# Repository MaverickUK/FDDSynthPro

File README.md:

# FDD Synth Duo

An RP2350 that pretends to be a 3.5-inch floppy drive, GoTek style, as the base for a future FDD Synth that *is* the drive rather than one that listens to it. Being the drive, it knows exactly when the motor spins and how the head moves, so the sounds can follow every step.

At this stage it is a proof of concept on an Olimex RP2350-PICO2-BB48, tested from the same Mac that builds it. The host is a Feather RP2040 with an Adafruit Floppy FeatherWing, running Adafruit's Greaseweazle-compatible firmware, so the Greaseweazle tools (`gw`) drive it. See [docs/plan.md](docs/plan.md) for the slices and [docs/wiring.md](docs/wiring.md) for the connections. [docs/bringup.md](docs/bringup.md) is the checklist for hardware day, [docs/parts.md](docs/parts.md) the parts list, and [docs/wiring.html](docs/wiring.html) an interactive wiring diagram with a soldering checklist (open it in a browser).

It follows the approach of [HDDSynthPro](https://github.com/MaverickUK/HDDSynthPro), which does the same for IDE hard disks.

## See and hear it

A 36-second showreel, with sound (click to play). A virtual PC uses a FAT12 disk while the front panel is worked: a disk chosen and swapped in, boot and `DIR`, reads with the volume turned down, the head trace following a long seek, a save, motor off and an eject. The screens, the drive and the sound are all the firmware's own code, run on the Mac in simulated real time, with the sample pack cut from a recording of a real drive (`samples/Recorded`). `scripts/make_showreel.py` makes it. (The link plays it through jsDelivr, which serves the repo's copy as a video; GitHub's own link would download it.)

## Status

Slice 0 (listen only): the firmware records every drive select, motor, side, density and write-gate change and every head step it sees, without driving any pin, and streams the trace over USB serial.

The drive build (`pio run -e bb48_drive`, slices 1-3) is ready for when the hardware arrives:
- it tracks the head, and drives TRK00, a 300 or 360 RPM index, write protect and disk change (or READY, for Shugart hosts);
- it streams an image from the SD card on RDATA, or, without one, a welcome disk whose `README.TXT` (from [welcome/README.TXT](welcome/README.TXT)) explains how to set the drive up: PC disks from 160 KB to 1.68 MB (5.25- and 3.5-inch) by their size, and other machines' disks, MFM or FM (Roland, Ensoniq, Kaypro, the Osborne 1, 8-inch CP/M and the like), from GoTek's `IMG.CFG`;
- it serves HFE flux images too: tracks as recorded, so copy-protected disks keep their bad CRCs, long tracks and weak bits;
- it takes writes back into the image, from single sectors to whole tracks;
- it swaps between the images on the card, GoTek style, whatever their formats;
- it answers as drive A or B, past a twist or on a straight cable, or as Shugart DS0–DS2; or as two drives at once, each with its own disk ([docs/config.md](docs/config.md));
- it reports what it does as sound events (motor, clicks, seeks, bumps against the end stops, disk changes), and plays them with a sample pack through an I2S amp: the FDD Synth. See [docs/activity.md](docs/activity.md), `samples/Recorded/` for a sample pack cut from a recording of a real drive, and `samples/Placeholder/` for a synthesised stand-in.

Its logic is tested on the Mac against virtual hosts (the Feather's firmware and a Greaseweazle's), and its PIO program in a simulator whose output Greaseweazle's own decoder reads back. It has not run on hardware yet.

## Front panel

An SSD1306 OLED on the BB48's Qwiic socket, a rotary encoder and an action button, as on the HDD Synth. Turn for the volume; press to pick a disk from the card and insert it; the action button steps through the screens, and holding it ejects the disk. On the Sounds screen, press to choose the sample pack. Like a GoTek, it remembers the disk, the pack and the volume across power-off. [docs/oled](docs/oled) has every screen, drawn by the firmware's own code.

## Quick start

```sh
test/run_native_tests.sh                 # C++ unit tests (no hardware)
brew install mtools dosfstools           # for the DOS disk tests
cd host && python3 -m venv .venv && .venv/bin/pip install -r requirements.txt
.venv/bin/pytest                         # simulator and parser tests (no hardware)

pio run -t upload                        # build and flash the BB48
pio device monitor                       # h help, p pin levels, s stats

scripts/rig.sh -m slice0                 # everything, against the real host
```

Read the power-order rule in [docs/wiring.md](docs/wiring.md) before connecting the host.

## Licence

To be decided (HDDSynth_Native is GPL-3.0).

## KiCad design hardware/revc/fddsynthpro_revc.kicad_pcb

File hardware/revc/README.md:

# FDD Synth Duo rev C board

The integrated board: the RP2350B with its flash and PSRAM, the microSD socket, the floppy interface, the MAX98357A amp, and power from the floppy power connector or USB-C, on rev B's outline (the HDD Synth MK5's). The design and the reasons for it are in [docs/pcb-revc.md](../../docs/pcb-revc.md); the sled that fits it in a 3.5-inch bay is [hardware/mount/fddsynthpro_bay.scad](../mount/fddsynthpro_bay.scad).

Status: **not reviewed, not ordered.** The schematic passes ERC with 0 violations, and its netlist test passes. The board is placed and autorouted: DRC with schematic parity finds 0 unconnected items and 0 parity issues; its 7 warnings are connector outlines overhanging the edge, as meant. `build.sh` rebuilds and checks it all.

## Files

| File | What |
|---|---|
| `fddsynthpro_revc.kicad_pro` | The project: open this in KiCad 10 |
| `fddsynthpro_revc.kicad_sch` | Root sheet, with one sheet per block: `power`, `mcu` (RP2350B, flash, PSRAM), `floppy`, `audio` (the amp and the panel headers), `sd` |
| `fddsynthpro_revc.kicad_pcb` | The board: 4 layers (signals, GND plane, 3V3 plane, signals) |
| `fddsynthpro_revc.kicad_dru` | One rule: 0.125 mm spacing inside Raspberry Pi's regulator layout only (HDDSynthPro's) |
| `FDDSynthProRevC.kicad_sym`, `FDDSynthProRevC.pretty/` | The SN7407 and LM66200 symbols; the floppy power header's footprint; the logo; Raspberry Pi's inductor and wide-0402 footprints and the TF PUSH microSD socket (HDDSynthPro's) |
| `tools/gen_schematic.py` | Generates the schematic, with each part's LCSC number |
| `tools/layout_pcb.py` | Places the parts, Raspberry Pi's regulator copper and the planes |
| `tools/autoroute.py` | Routes with Freerouting, then pours ground on the outer layers |
| `tools/make_logo.py` | Makes the silkscreen logo and the easter egg on the back (board-only footprints) from `media/FDDSynthDuo.png` and `media/dont-copy-that-floppy.png` |
| `tools/add_parts.py` | Adds parts the schematic has gained to the routed board, or moves parts on it (`--move`), so only their nets get routed |

The generators follow HDDSynthPro's (`../../HDDSynthPro/hardware/tools`). They bootstrap the design: once the files are edited in KiCad, those edits are the source, and rerunning a generator overwrites them.

To add a small part to the routed board without routing it all again (where there's room: the series resistors on the floppy inputs needed a full reroute, `build.sh`): add it to `gen_schematic.py` and to `PLACE` in `layout_pcb.py`, then

```sh
python tools/gen_schematic.py
"$KICAD_PYTHON" tools/add_parts.py prepare      # places it, locks the routing that's there
                                               # (or: prepare --move J5, to move a part and reroute its nets;
                                               #  prepare --rip NET, to route one net again)
FREEROUTING=... JAVA=... "$KICAD_PYTHON" tools/autoroute.py
"$KICAD_PYTHON" tools/add_parts.py finish       # unlocks it again
./build.sh --silkscreen
```

## Building and checking it

KiCad 10 is needed (the files are KiCad 10's format). On the Windows machine, a portable KiCad 10 lives in `%LOCALAPPDATA%\Programs\kicad10-portable`. It was unpacked from the installer, so it needs no admin rights, and its `env.sh` sets `KICAD_CLI`, `KICAD_PYTHON` and the library paths. Freerouting 2.5.0 and a Java 25 runtime are in `%LOCALAPPDATA%\Programs\freerouting`.

```sh
. "$LOCALAPPDATA/Programs/kicad10-portable/env.sh"
cd hardware/revc
python tools/gen_schematic.py                                   # the schematic
"$KICAD_CLI" sch erc fddsynthpro_revc.kicad_sch                 # expect 0 violations
"$KICAD_PYTHON" tools/layout_pcb.py                             # placement (overwrites the board)
FREEROUTING=<freerouting-2.5.0.jar> JAVA=<java.exe> "$KICAD_PYTHON" tools/autoroute.py
"$KICAD_CLI" pcb drc --refill-zones --save-board --schematic-parity fddsynthpro_revc.kicad_pcb
cd ../../host && KICAD_CLI="$KICAD_CLI" pytest tests/test_revc_schematic.py   # the netlist against src/config.h
```

On the Mac, KiCad's own paths work as for rev B: `KICAD_SHARE=/Applications/KiCad/KiCad.app/Contents/SharedSupport`, and KiCad's bundled Python for the layout and routing scripts.

## Ordering

Every part carries its LCSC number in a `LCSC Part Number` field (the Fabrication Toolkit plugin reads it). [docs/pcb-revc.md](../../docs/pcb-revc.md) lists the parts and their stock on 8 Nov 2026. Check these before ordering:
- **L1** (Raspberry Pi's 3.3 µH inductor) was out of stock.
- **The 16 MB flash** was down to 20.
- **J12,** the HDD Synth-style speaker terminal, is marked DNP (not fitted).
- **Solder mask:** the RP2350B (U1), USB-C (J9) and LM66200 (U6) footprints are copies of KiCad's (`gen_schematic.py`'s `one_mask_opening()`) with one mask opening per row of fine-pitch pads. Their pads are 0.2 mm apart, and PCBWay can't make a strip of black mask under 0.22 mm (it asked about the IDE Synth Bay's QFN-80, 11 Nov 2026). The narrowest strip left is 0.25 mm, so black mask needs no special request.
- **JLCPCB's placement preview:** check the rotations, above all the QFN-80, the inductor's polarity dot, the SOT-583, the TQFN-16 and the right-angle J1.

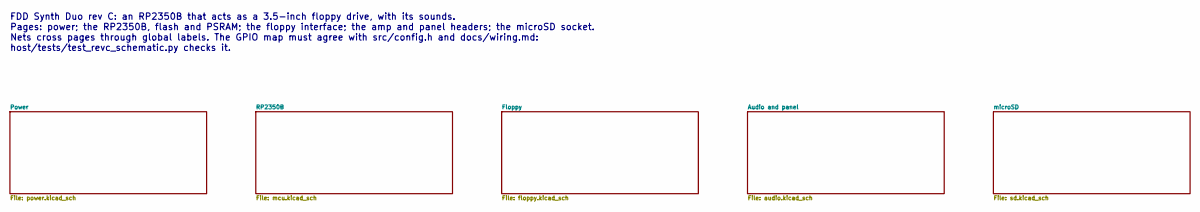
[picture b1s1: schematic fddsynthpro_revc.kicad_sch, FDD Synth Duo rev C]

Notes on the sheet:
FDD Synth Duo rev C: an RP2350B that acts as a 3.5-inch floppy drive, with its sounds. Pages: power; the RP2350B, flash and PSRAM; the floppy interface; the amp and panel headers; the microSD socket. Nets cross pages through global labels. The GPIO map must agree with src/config.h and docs/wiring.m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

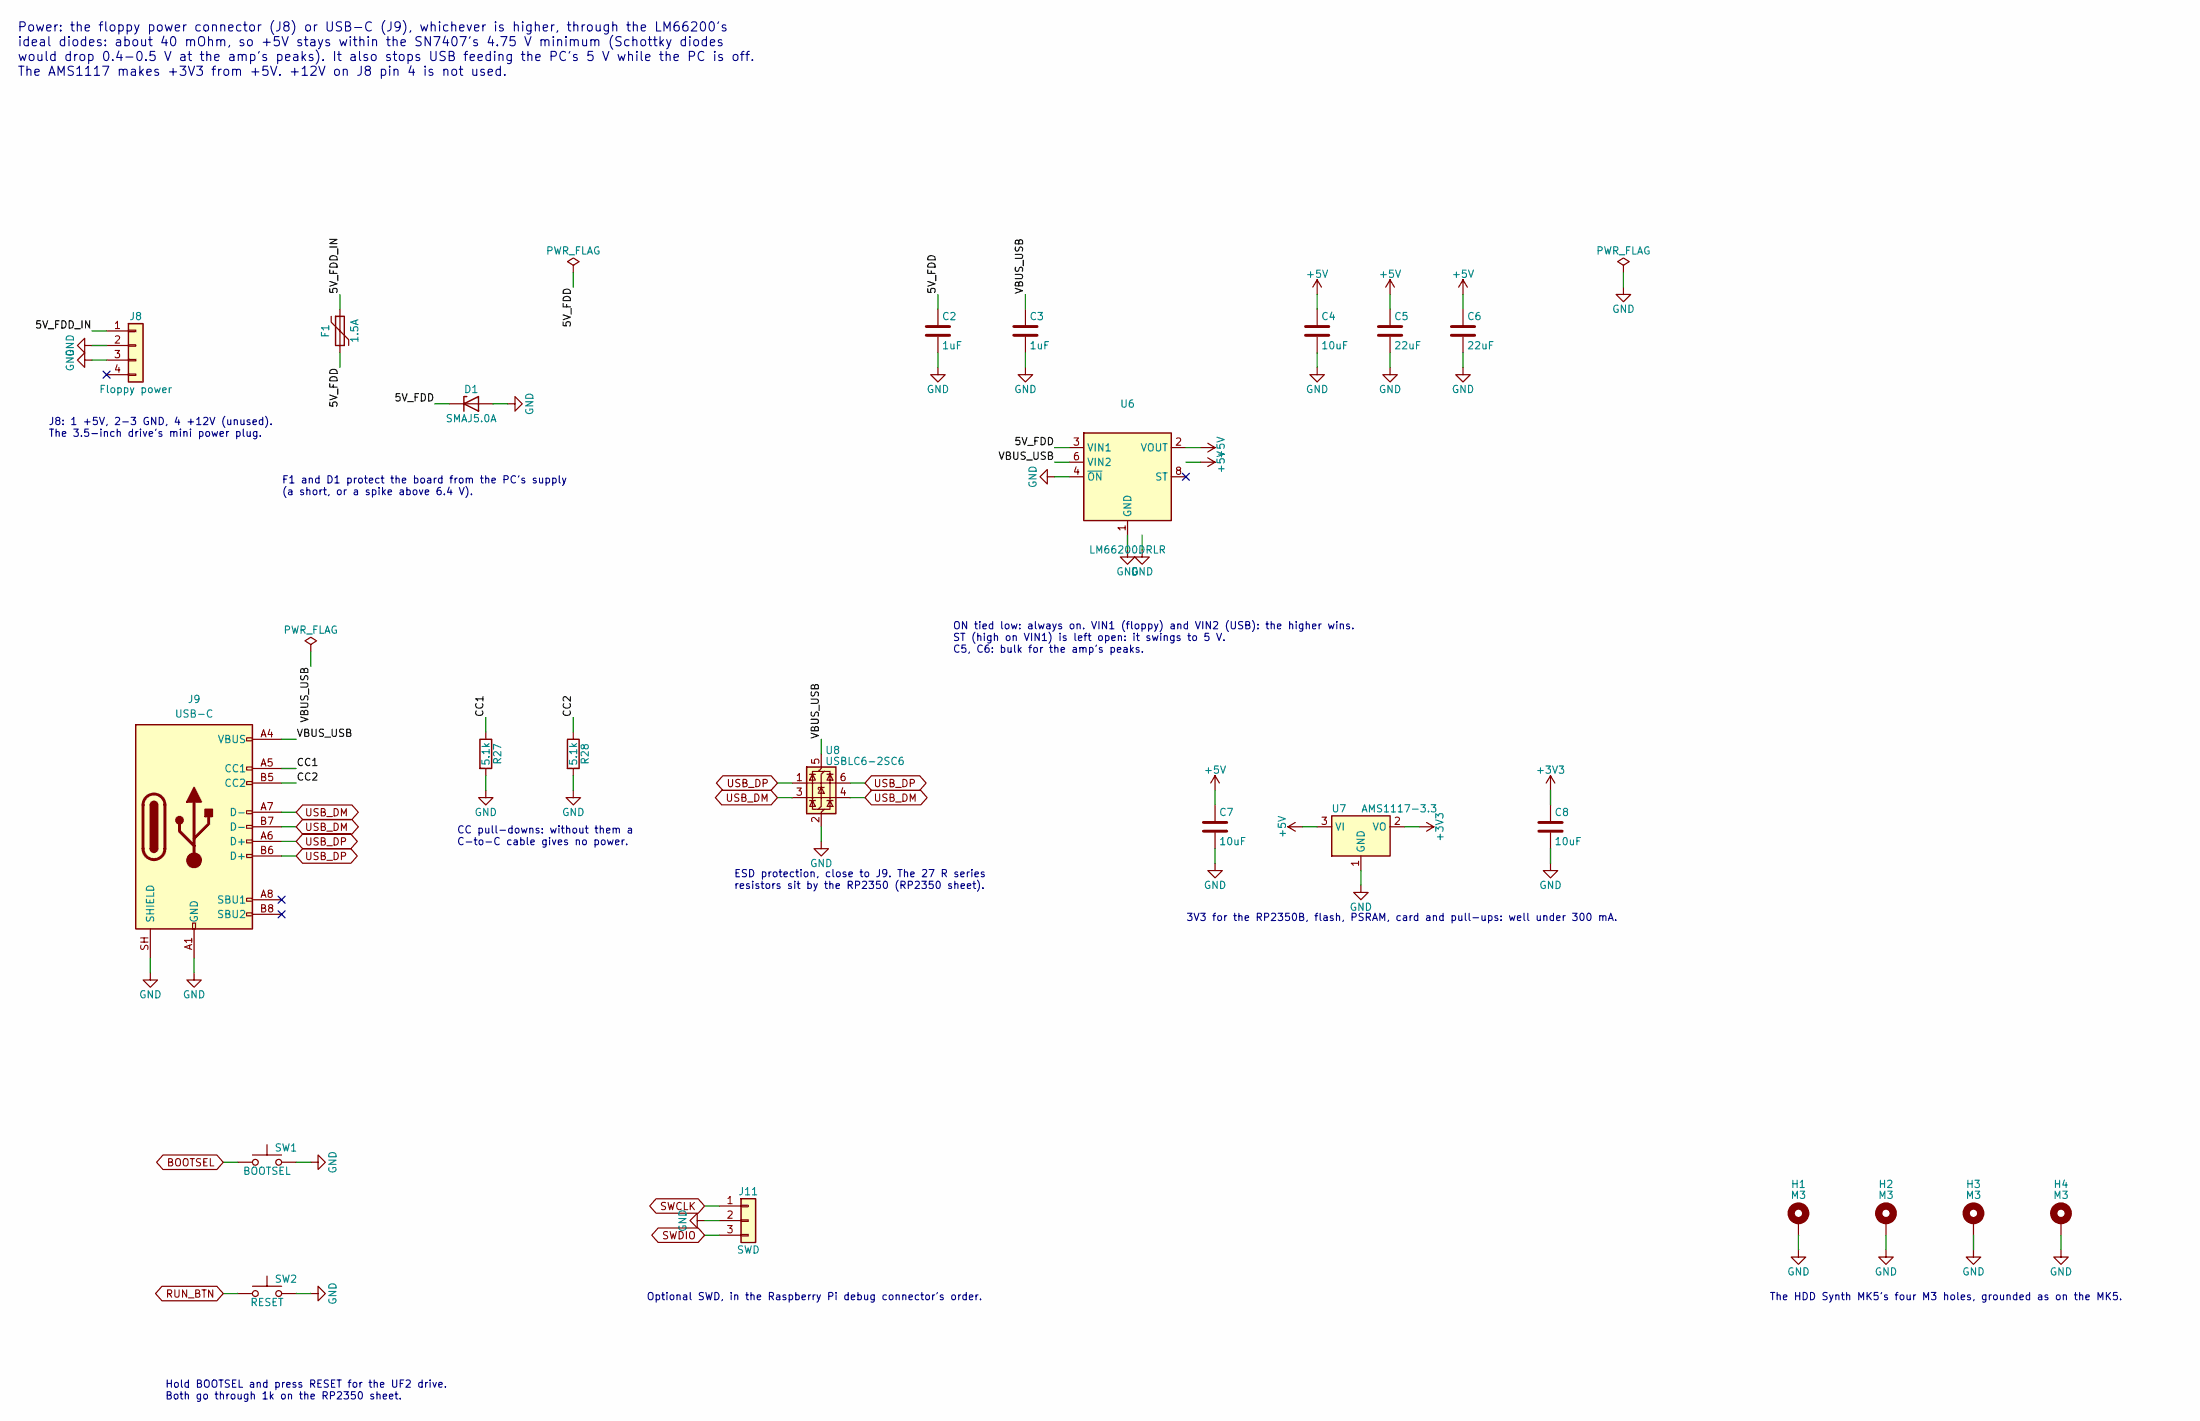
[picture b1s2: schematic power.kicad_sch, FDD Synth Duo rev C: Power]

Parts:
C2, C3: 1uF; C_0402_1005Metric; LCSC Part Number C52923
C4, C7, C8: 10uF; C_0805_2012Metric; LCSC Part Number C15850
C5, C6: 22uF; C_0603_1608Metric; LCSC Part Number C59461
D1: SMAJ5.0A; D_SMA; LCSC Part Number C113952
F1: 1.5A; Fuse_1206_3216Metric; LCSC Part Number C2830250
H1, H2, H3, H4: M3; MountingHole_3.2mm_M3_Pad
J8: Floppy power; TE_171825-4_1x04_P2.50mm_Vertical; MPN TE 171825-4; LCSC Part Number C210162
J9: USB-C; USB_C_Receptacle_HRO_TYPE-C-31-M-12_OneMaskOpening; MPN HRO TYPE-C-31-M-12; LCSC Part Number C165948
J11: SWD; PinHeader_1x03_P2.54mm_Vertical; LCSC Part Number C124376
R27, R28: 5.1k; R_0603_1608Metric; LCSC Part Number C23186
SW1: BOOTSEL; SW_Push_1P1T_XKB_TS-1187A; LCSC Part Number C318884
SW2: RESET; SW_Push_1P1T_XKB_TS-1187A; LCSC Part Number C318884
U6: LM66200DRLR; SOT-583-8_OneMaskOpening; LCSC Part Number C3235556
U7: AMS1117-3.3; SOT-223-3_TabPin2; LCSC Part Number C6186
U8: USBLC6-2SC6; SOT-23-6; LCSC Part Number C2687116

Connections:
+3V3: C8.1, U7.2 (VO); also elsewhere on the board
+5V: C4.1, C5.1, C6.1, C7.1, U6.2 (VOUT), U6.7 (VOUT), U7.3 (VI); also elsewhere on the board
/Power/5V_FDD: C2.1, D1.1 (K), F1.2, U6.3 (VIN1)
/Power/5V_FDD_IN: F1.1, J8.1
/Power/CC1: J9.A5 (CC1), R27.1
/Power/CC2: J9.B5 (CC2), R28.1
/Power/VBUS_USB: C3.1, J9.A4 (VBUS), J9.A9 (VBUS), J9.B4 (VBUS), J9.B9 (VBUS), U6.6 (VIN2), U8.5 (VBUS)
BOOTSEL: SW1.1; also elsewhere on the board
GND: C2.2, C3.2, C4.2, C5.2, C6.2, C7.2, C8.2, D1.2 (A), H1.1, H2.1, H3.1, H4.1, J8.2, J8.3, J9.A1 (GND), J9.A12 (GND), J9.B1 (GND), J9.B12 (GND), J9.SH (SHIELD), J11.2, R27.2, R28.2, SW1.2, SW2.2, U6.1 (GND), U6.4 (~ON), U6.5 (GND), U7.1 (GND), U8.2 (GND); also elsewhere on the board
RUN_BTN: SW2.1; also elsewhere on the board
SWCLK: J11.1; also elsewhere on the board
SWDIO: J11.3; also elsewhere on the board
USB_DM: J9.A7 (D-), J9.B7 (D-), U8.3 (I/O2), U8.4 (I/O2); also elsewhere on the board
USB_DP: J9.A6 (D+), J9.B6 (D+), U8.1 (I/O1), U8.6 (I/O1); also elsewhere on the board

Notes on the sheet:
Power: the floppy power connector (J8) or USB-C (J9), whichever is higher, through the LM66200's ideal diodes: about 40 mOhm, so +5V stays within the SN7407's 4.75 V minimum (Schottky diodes would drop 0.4-0.5 V at the amp's peaks). It also stops USB feeding the PC's 5 V while the PC is off. The AM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
J8: 1 +5V, 2-3 GND, 4 +12V (unused). The 3.5-inch drive's mini power plug.
F1 and D1 protect the board from the PC's supply (a short, or a spike above 6.4 V).
CC pull-downs: without them a C-to-C cable gives no power.
ESD protection, close to J9. The 27 R series resistors sit by the RP2350 (RP2350 sheet).
ON tied low: always on. VIN1 (floppy) and VIN2 (USB): the higher wins. ST (high on VIN1) is left open: it swings to 5 V. C5, C6: bulk for the amp's peaks.
3V3 for the RP2350B, flash, PSRAM, card and pull-ups: well under 300 mA.
Hold BOOTSEL and press RESET for the UF2 drive. Both go through 1k on the RP2350 sheet.
Optional SWD, in the Raspberry Pi debug connector's order.
The HDD Synth MK5's four M3 holes, grounded as on the MK5.

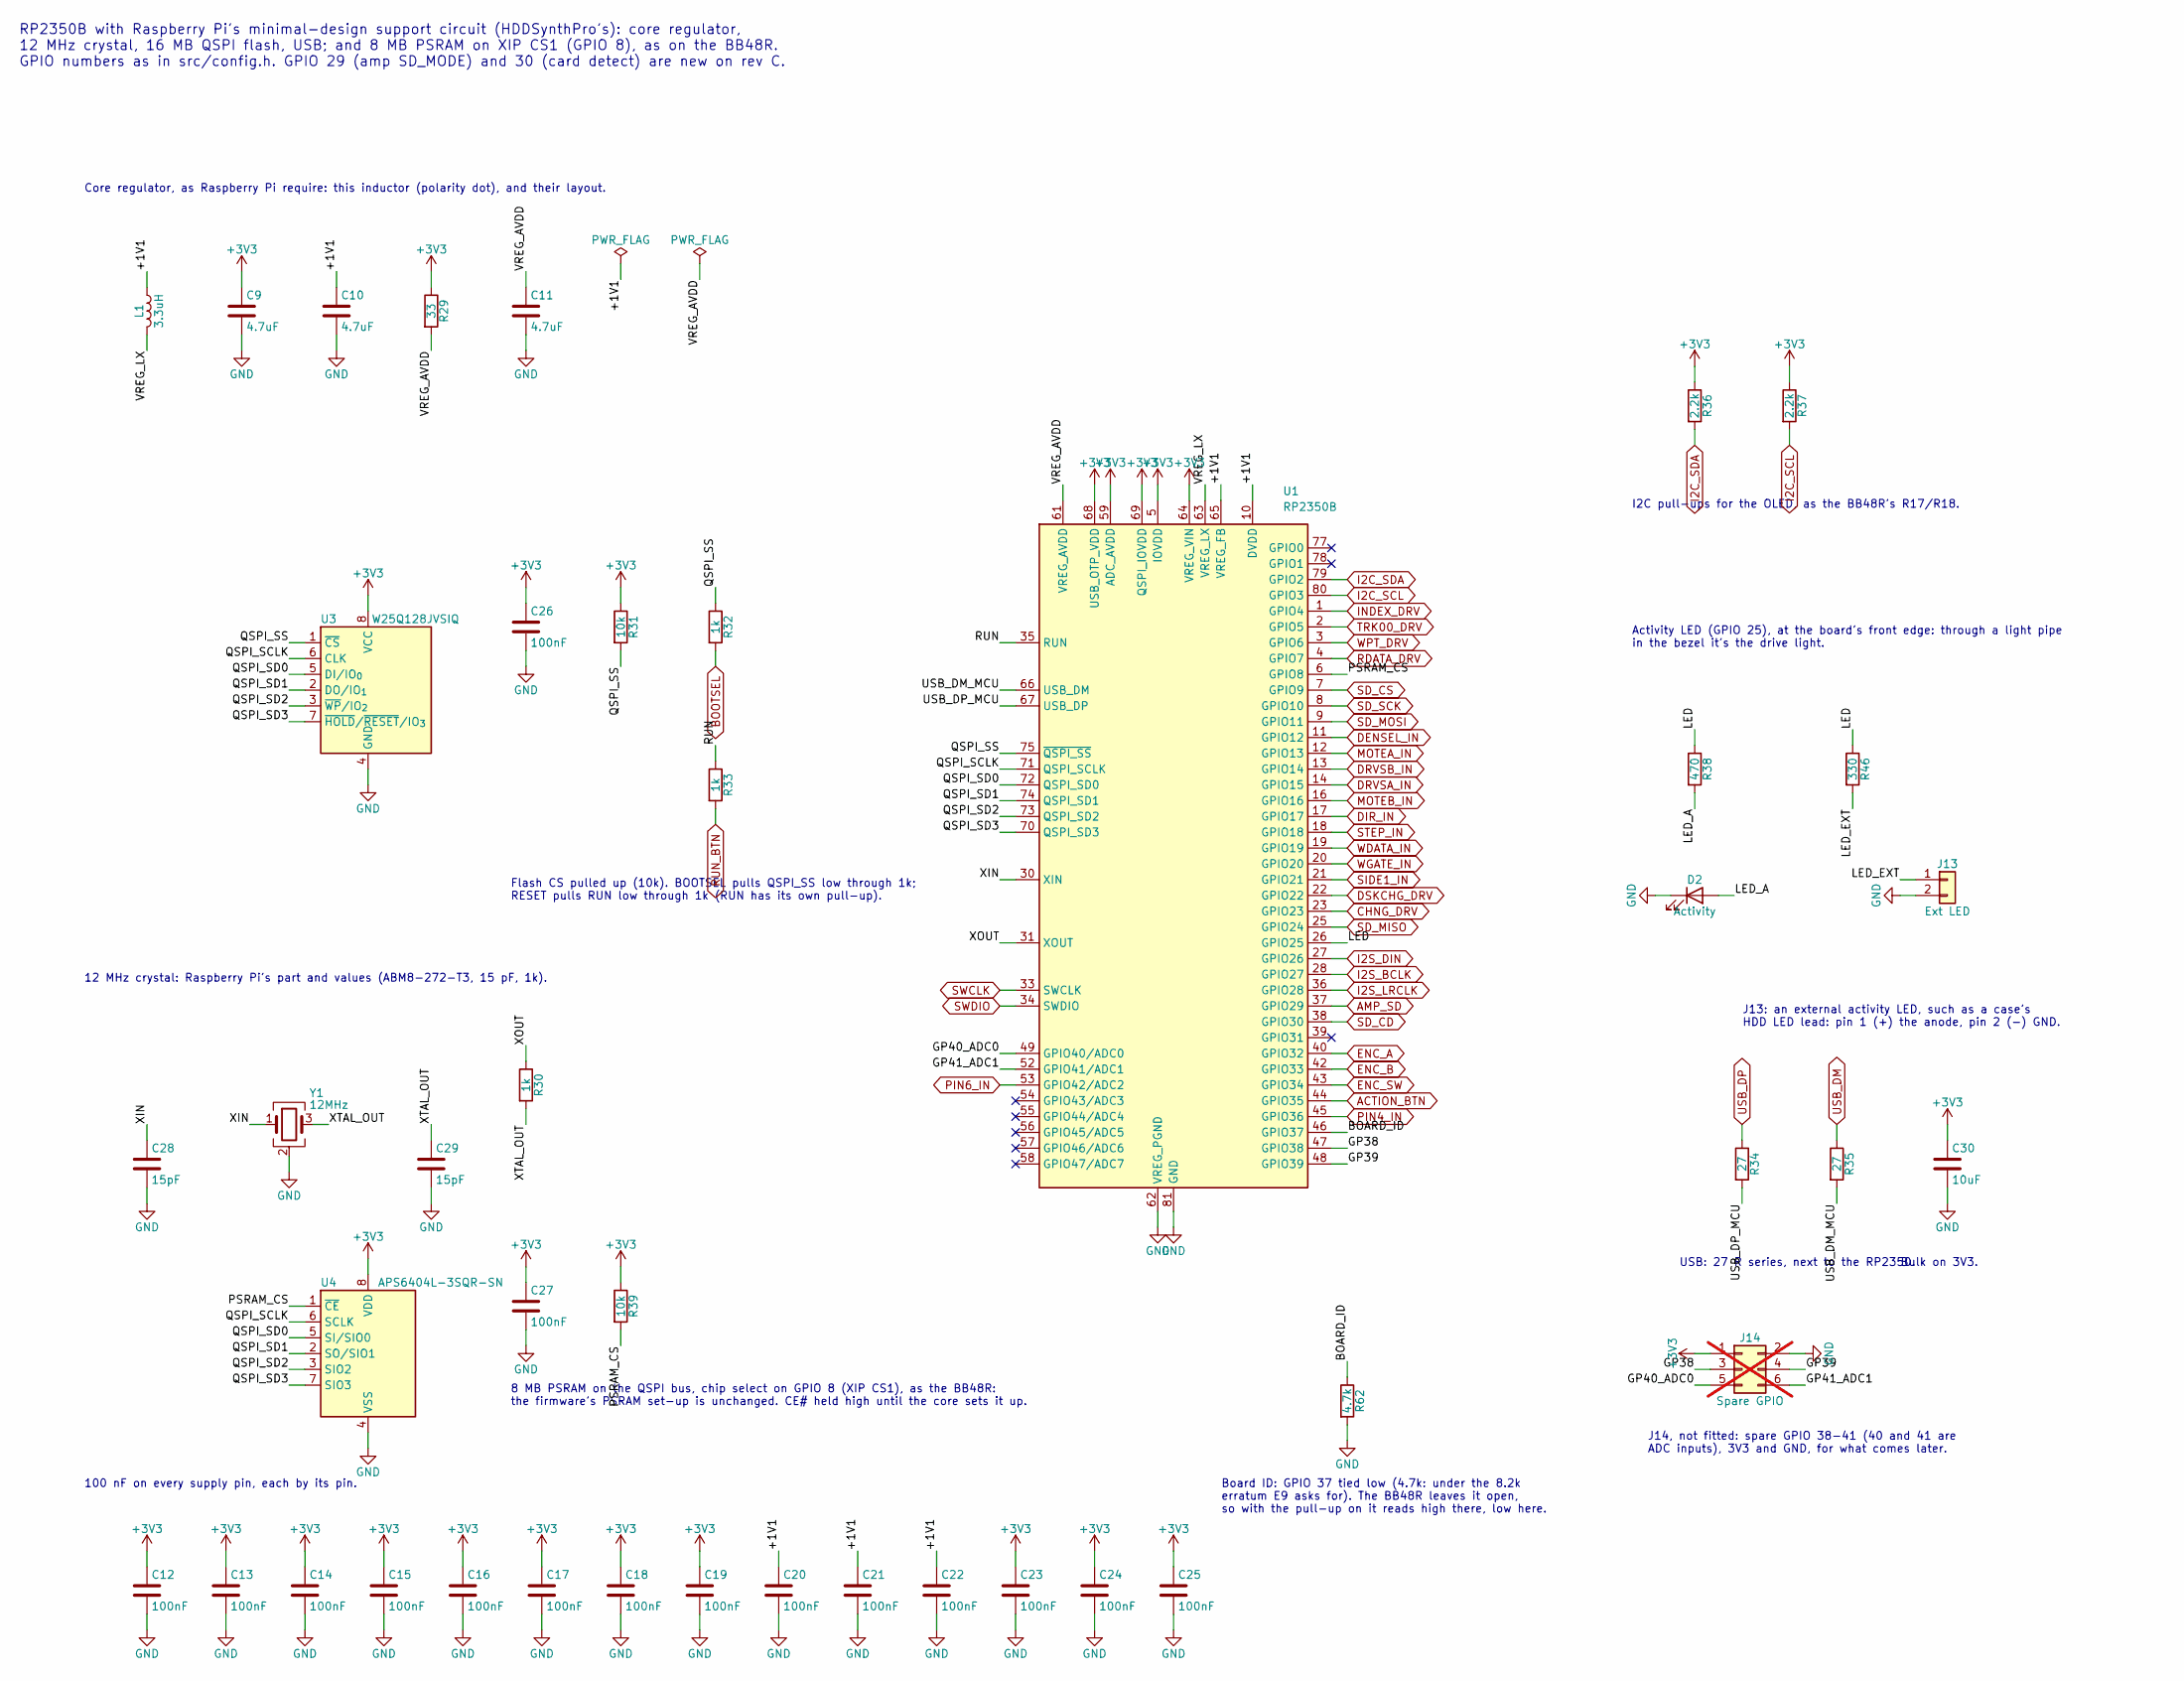
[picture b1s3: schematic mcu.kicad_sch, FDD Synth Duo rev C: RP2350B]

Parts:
C9, C10: 4.7uF; C_0402_1005Metric_RPi_Wide; LCSC Part Number C23733
C11: 4.7uF; C_0402_1005Metric; LCSC Part Number C23733
C12, C13, C14, C15, C16, C17, C18, C19, C20, C21, C22, C23, C24, C25, C26, C27: 100nF; C_0402_1005Metric; LCSC Part Number C1525
C28, C29: 15pF; C_0402_1005Metric; LCSC Part Number C1548
C30: 10uF; C_0805_2012Metric; LCSC Part Number C15850
D2: Activity; LED_0805_2012Metric; LCSC Part Number C2297
J13: Ext LED; PinHeader_1x02_P2.54mm_Vertical; LCSC Part Number C124375
J14: Spare GPIO; PinHeader_2x03_P2.54mm_Vertical; not fitted
L1: 3.3uH; L_Abracon_AOTA-B201610S3R3; MPN Abracon AOTA-B201610S3R3-101-T; LCSC Part Number C42411119
R29: 33; R_0402_1005Metric; LCSC Part Number C25105
R30, R32, R33: 1k; R_0402_1005Metric; LCSC Part Number C11702
R31, R39: 10k; R_0402_1005Metric; LCSC Part Number C25744
R34, R35: 27; R_0402_1005Metric; LCSC Part Number C25100
R36, R37: 2.2k; R_0402_1005Metric; LCSC Part Number C25879
R38: 470; R_0402_1005Metric; LCSC Part Number C25117
R46: 330; R_0402_1005Metric; LCSC Part Number C25104
R62: 4.7k; R_0402_1005Metric; LCSC Part Number C25900
U1: RP2350B; QFN-80-1EP_10x10mm_P0.4mm_EP3.4x3.4mm_ThermalVias_OneMaskOp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; LCSC Part Number C42415655
U3: W25Q128JVSIQ; SOIC-8_5.3x5.3mm_P1.27mm; LCSC Part Number C97521
U4: APS6404L-3SQR-SN; SOIC-8_3.9x4.9mm_P1.27mm; LCSC Part Number C5333729
Y1: 12MHz; Crystal_SMD_3225-4Pin_3.2x2.5mm; MPN Abracon ABM8-272-T3; LCSC Part Number C20625731

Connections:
+3V3: C9.1, C12.1, C13.1, C14.1, C15.1, C16.1, C17.1, C18.1, C19.1, C23.1, C24.1, C25.1, C26.1, C27.1, C30.1, J14.1, R29.1, R31.1, R36.1, R37.1, R39.1, U1.5 (IOVDD), U1.15 (IOVDD), U1.24 (IOVDD), U1.29 (IOVDD), U1.41 (IOVDD), U1.50 (IOVDD), U1.59 (ADC_AVDD), U1.60 (IOVDD), U1.64 (VREG_VIN), U1.68 (USB_OTP_VDD), U1.69 (QSPI_IOVDD), U1.76 (IOVDD), U3.8 (VCC), U4.8 (VDD); also elsewhere on the board
/RP2350B/+1V1: C10.1, C20.1, C21.1, C22.1, L1.1, U1.10 (DVDD), U1.32 (DVDD), U1.51 (DVDD), U1.65 (VREG_FB)
/RP2350B/BOARD_ID: R62.1, U1.46 (GPIO37)
/RP2350B/GP38: J14.3, U1.47 (GPIO38)
/RP2350B/GP39: J14.4, U1.48 (GPIO39)
/RP2350B/GP40_ADC0: J14.5, U1.49 (GPIO40/ADC0)
/RP2350B/GP41_ADC1: J14.6, U1.52 (GPIO41/ADC1)
/RP2350B/LED: R38.1, R46.1, U1.26 (GPIO25)
/RP2350B/LED_A: D2.2 (A), R38.2
/RP2350B/LED_EXT: J13.1, R46.2
/RP2350B/PSRAM_CS: R39.2, U1.6 (GPIO8), U4.1 (~CE)
/RP2350B/QSPI_SCLK: U1.71 (QSPI_SCLK), U3.6 (CLK), U4.6 (SCLK)
/RP2350B/QSPI_SD0: U1.72 (QSPI_SD0), U3.5 (DI/IO_{0}), U4.5 (SI/SIO0)
/RP2350B/QSPI_SD1: U1.74 (QSPI_SD1), U3.2 (DO/IO_{1}), U4.2 (SO/SIO1)
/RP2350B/QSPI_SD2: U1.73 (QSPI_SD2), U3.3 (~WP/IO_{2}), U4.3 (SIO2)
/RP2350B/QSPI_SD3: U1.70 (QSPI_SD3), U3.7 (~HOLD/~RESET/IO_{3}), U4.7 (SIO3)
/RP2350B/QSPI_SS: R31.2, R32.1, U1.75 (~QSPI_SS), U3.1 (~CS)
/RP2350B/RUN: R33.1, U1.35 (RUN)
/RP2350B/USB_DM_MCU: R35.2, U1.66 (USB_DM)
/RP2350B/USB_DP_MCU: R34.2, U1.67 (USB_DP)
/RP2350B/VREG_AVDD: C11.1, R29.2, U1.61 (VREG_AVDD)
/RP2350B/VREG_LX: L1.2, U1.63 (VREG_LX)
/RP2350B/XIN: C28.1, U1.30 (XIN), Y1.1
/RP2350B/XOUT: R30.1, U1.31 (XOUT)
/RP2350B/XTAL_OUT: C29.1, R30.2, Y1.3
ACTION_BTN: U1.44 (GPIO35); also elsewhere on the board
AMP_SD: U1.37 (GPIO29); also elsewhere on the board
BOOTSEL: R32.2; also elsewhere on the board
CHNG_DRV: U1.23 (GPIO23); also elsewhere on the board
DENSEL_IN: U1.11 (GPIO12); also elsewhere on the board
DIR_IN: U1.17 (GPIO17); also elsewhere on the board
DRVSA_IN: U1.14 (GPIO15); also elsewhere on the board
DRVSB_IN: U1.13 (GPIO14); also elsewhere on the board
DSKCHG_DRV: U1.22 (GPIO22); also elsewhere on the board
ENC_A: U1.40 (GPIO32); also elsewhere on the board
ENC_B: U1.42 (GPIO33); also elsewhere on the board
ENC_SW: U1.43 (GPIO34); also elsewhere on the board
GND: C9.2, C10.2, C11.2, C12.2, C13.2, C14.2, C15.2, C16.2, C17.2, C18.2, C19.2, C20.2, C21.2, C22.2, C23.2, C24.2, C25.2, C26.2, C27.2, C28.2, C29.2, C30.2, D2.1 (K), J13.2, J14.2, R62.2, U1.62 (VREG_PGND), U1.81 (GND), U3.4 (GND), U4.4 (VSS), Y1.2 (G), Y1.4 (G); also elsewhere on the board
I2C_SCL: R37.2, U1.80 (GPIO3); also elsewhere on the board
I2C_SDA: R36.2, U1.79 (GPIO2); also elsewhere on the board
I2S_BCLK: U1.28 (GPIO27); also elsewhere on the board
I2S_DIN: U1.27 (GPIO26); also elsewhere on the board
I2S_LRCLK: U1.36 (GPIO28); also elsewhere on the board
INDEX_DRV: U1.1 (GPIO4); also elsewhere on the board
MOTEA_IN: U1.12 (GPIO13); also elsewhere on the board
MOTEB_IN: U1.16 (GPIO16); also elsewhere on the board
PIN4_IN: U1.45 (GPIO36); also elsewhere on the board
PIN6_IN: U1.53 (GPIO42/ADC2); also elsewhere on the board
RDATA_DRV: U1.4 (GPIO7); also elsewhere on the board
RUN_BTN: R33.2; also elsewhere on the board
SD_CD: U1.38 (GPIO30); also elsewhere on the board
SD_CS: U1.7 (GPIO9); also elsewhere on the board
SD_MISO: U1.25 (GPIO24); also elsewhere on the board
SD_MOSI: U1.9 (GPIO11); also elsewhere on the board
SD_SCK: U1.8 (GPIO10); also elsewhere on the board
SIDE1_IN: U1.21 (GPIO21); also elsewhere on the board
STEP_IN: U1.18 (GPIO18); also elsewhere on the board
SWCLK: U1.33 (SWCLK); also elsewhere on the board
SWDIO: U1.34 (SWDIO); also elsewhere on the board
TRK00_DRV: U1.2 (GPIO5); also elsewhere on the board
USB_DM: R35.1; also elsewhere on the board
USB_DP: R34.1; also elsewhere on the board
WDATA_IN: U1.19 (GPIO19); also elsewhere on the board
WGATE_IN: U1.20 (GPIO20); also elsewhere on the board
WPT_DRV: U1.3 (GPIO6); also elsewhere on the board

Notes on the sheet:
RP2350B with Raspberry Pi's minimal-design support circuit (HDDSynthPro's): core regulator, 12 MHz crystal, 16 MB QSPI flash, USB; and 8 MB PSRAM on XIP CS1 (GPIO 8), as on the BB48R. GPIO numbers as in src/config.h. GPIO 29 (amp SD_MODE) and 30 (card detect) are new on rev C.
Core regulator, as Raspberry Pi require: this inductor (polarity dot), and their layout.
100 nF on every supply pin, each by its pin.
12 MHz crystal: Raspberry Pi's part and values (ABM8-272-T3, 15 pF, 1k).
Flash CS pulled up (10k). BOOTSEL pulls QSPI_SS low through 1k; RESET pulls RUN low through 1k (RUN has its own pull-up).
8 MB PSRAM on the QSPI bus, chip select on GPIO 8 (XIP CS1), as the BB48R: the firmware's PSRAM set-up is unchanged. CE# held high until the core sets it up.
USB: 27 R series, next to the RP2350.
Bulk on 3V3.
I2C pull-ups for the OLED, as the BB48R's R17/R18.
Activity LED (GPIO 25), at the board's front edge: through a light pipe in the bezel it's the drive light.
J13: an external activity LED, such as a case's HDD LED lead: pin 1 (+) the anode, pin 2 (-) GND.
Board ID: GPIO 37 tied low (4.7k: under the 8.2k erratum E9 asks for). The BB48R leaves it open, so with the pull-up on it reads high there, low here.
J14, not fitted: spare GPIO 38-41 (40 and 41 are ADC inputs), 3V3 and GND, for what comes later.

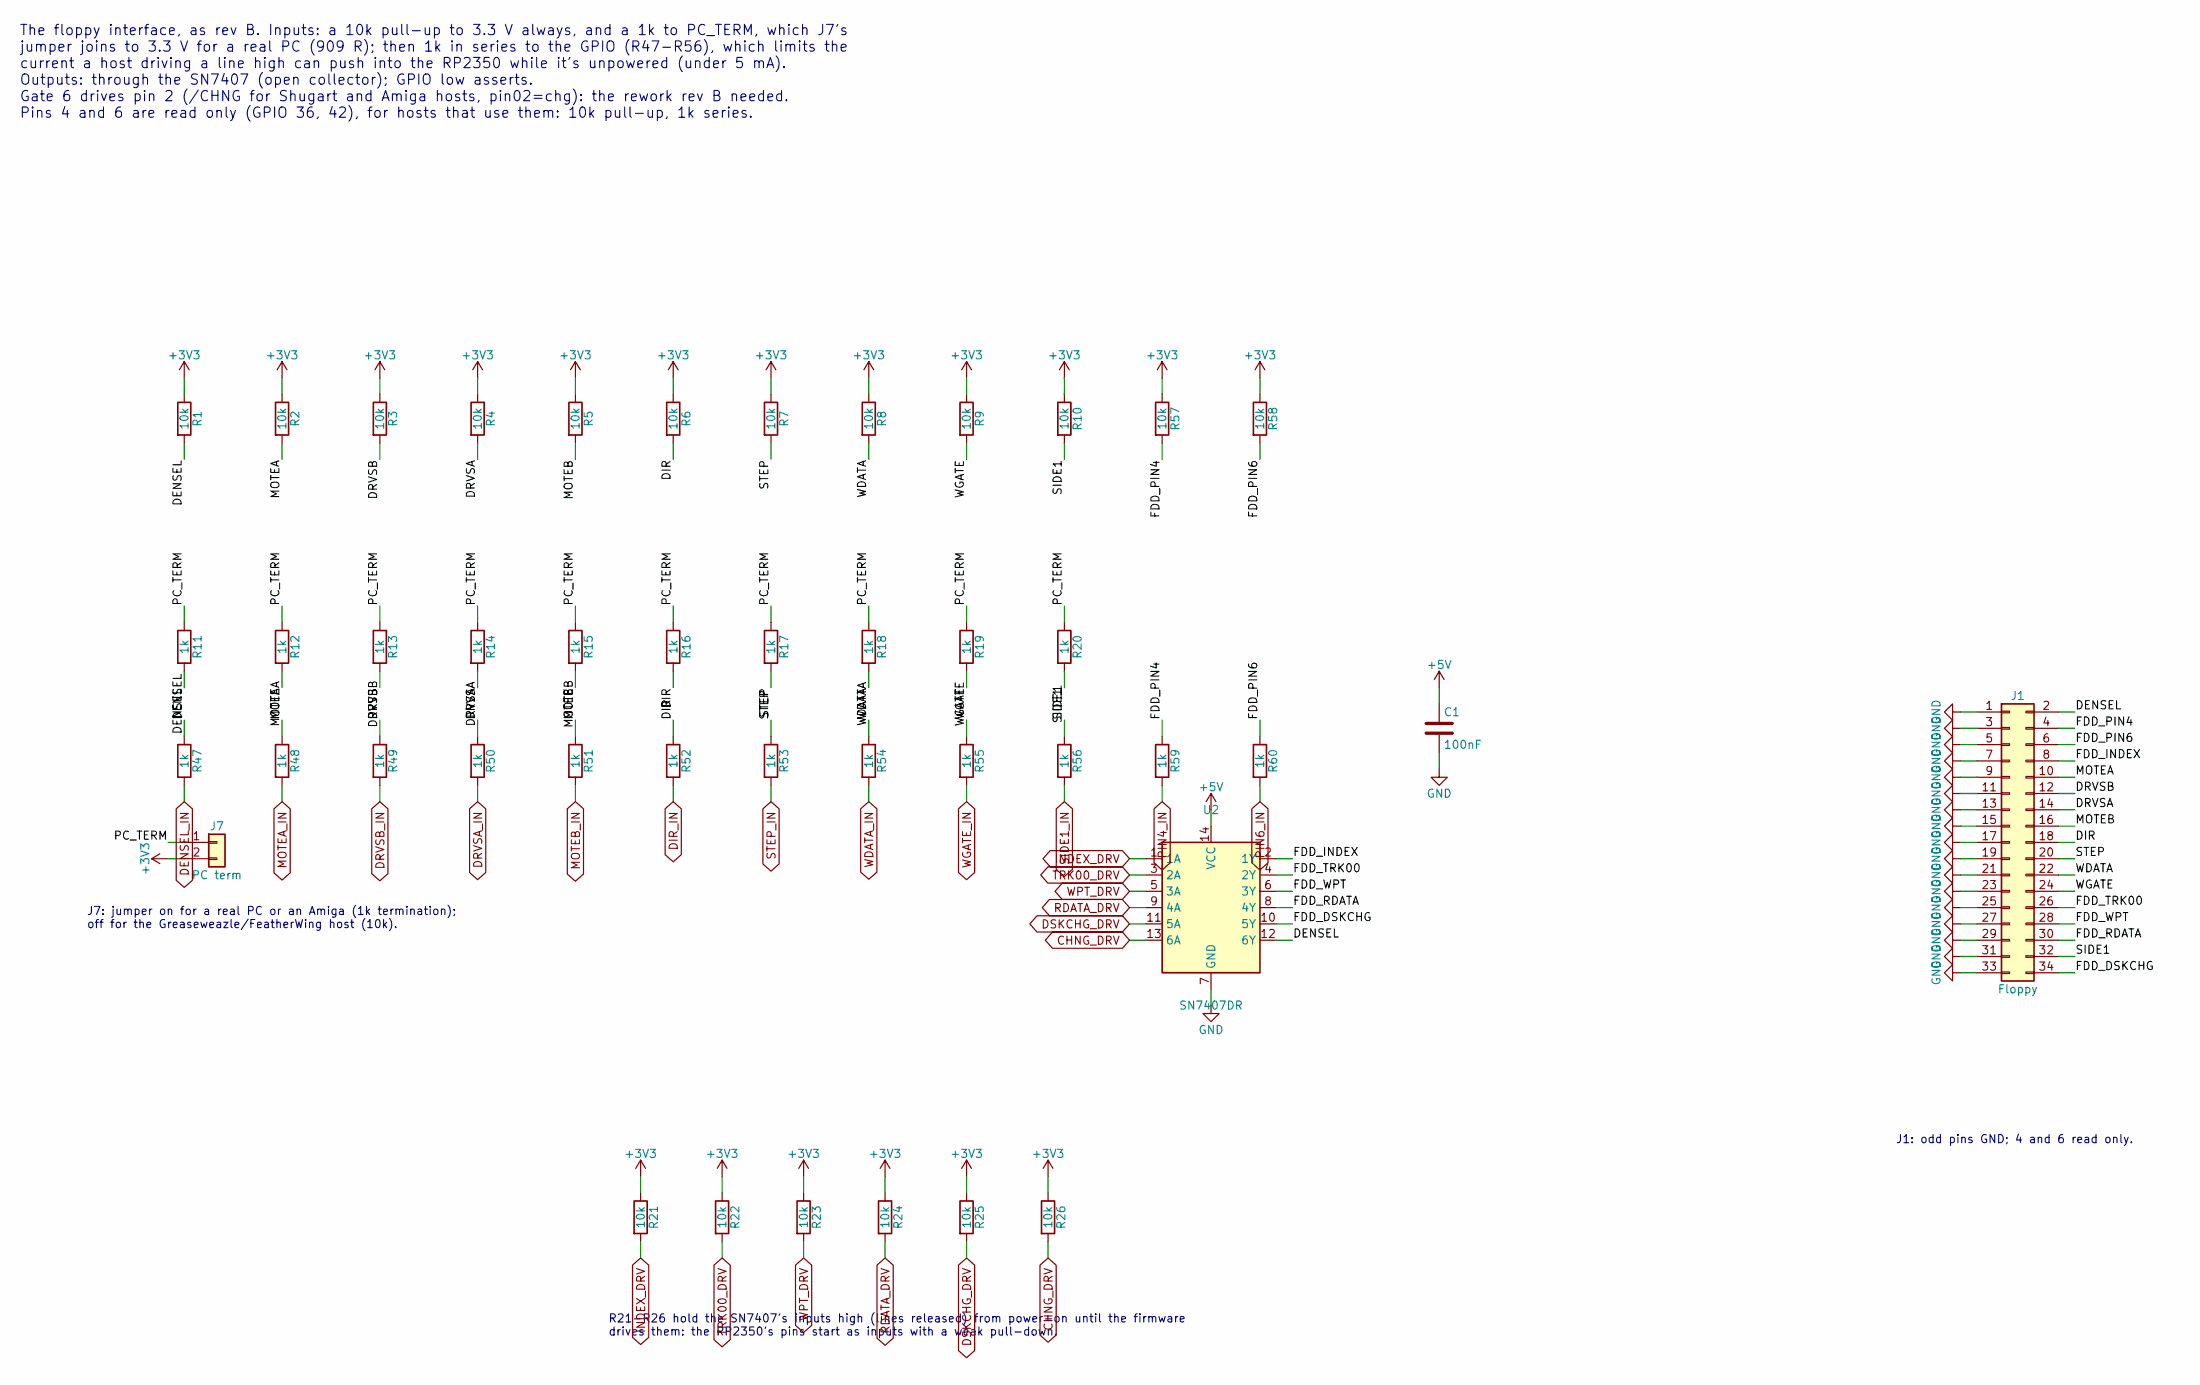
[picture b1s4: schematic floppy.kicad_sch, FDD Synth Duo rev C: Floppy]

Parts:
C1: 100nF; C_0402_1005Metric; LCSC Part Number C1525
J1: Floppy; IDC-Header_2x17_P2.54mm_Horizontal; MPN XFCN BH254R-34P (right angle, shrouded); LCSC Part Number C48603650
J7: PC term; PinHeader_1x02_P2.54mm_Vertical; LCSC Part Number C124375
R1, R2, R3, R4, R5, R6, R7, R8, R9, R10, R21, R22, R23, R24, R25, R26, R57, R58: 10k; R_0402_1005Metric; LCSC Part Number C25744
R11, R12, R13, R14, R15, R16, R17, R18, R19, R20, R47, R48, R49, R50, R51, R52, R53, R54, R55, R56, R59, R60: 1k; R_0402_1005Metric; LCSC Part Number C11702
U2: SN7407DR; SOIC-14_3.9x8.7mm_P1.27mm; LCSC Part Number C40481

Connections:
+3V3: J7.2, R1.1, R2.1, R3.1, R4.1, R5.1, R6.1, R7.1, R8.1, R9.1, R10.1, R21.1, R22.1, R23.1, R24.1, R25.1, R26.1, R57.1, R58.1; also elsewhere on the board
+5V: C1.1, U2.14 (VCC); also elsewhere on the board
/Floppy/DENSEL: J1.2, R1.2, R11.2, R47.1, U2.12 (6Y)
/Floppy/DIR: J1.18, R6.2, R16.2, R52.1
/Floppy/DRVSA: J1.14, R4.2, R14.2, R50.1
/Floppy/DRVSB: J1.12, R3.2, R13.2, R49.1
/Floppy/FDD_DSKCHG: J1.34, U2.10 (5Y)
/Floppy/FDD_INDEX: J1.8, U2.2 (1Y)
/Floppy/FDD_PIN4: J1.4, R57.2, R59.1
/Floppy/FDD_PIN6: J1.6, R58.2, R60.1
/Floppy/FDD_RDATA: J1.30, U2.8 (4Y)
/Floppy/FDD_TRK00: J1.26, U2.4 (2Y)
/Floppy/FDD_WPT: J1.28, U2.6 (3Y)
/Floppy/MOTEA: J1.10, R2.2, R12.2, R48.1
/Floppy/MOTEB: J1.16, R5.2, R15.2, R51.1
/Floppy/PC_TERM: J7.1, R11.1, R12.1, R13.1, R14.1, R15.1, R16.1, R17.1, R18.1, R19.1, R20.1
/Floppy/SIDE1: J1.32, R10.2, R20.2, R56.1
/Floppy/STEP: J1.20, R7.2, R17.2, R53.1
/Floppy/WDATA: J1.22, R8.2, R18.2, R54.1
/Floppy/WGATE: J1.24, R9.2, R19.2, R55.1
CHNG_DRV: R26.2, U2.13 (6A); also elsewhere on the board
DENSEL_IN: R47.2; also elsewhere on the board
DIR_IN: R52.2; also elsewhere on the board
DRVSA_IN: R50.2; also elsewhere on the board
DRVSB_IN: R49.2; also elsewhere on the board
DSKCHG_DRV: R25.2, U2.11 (5A); also elsewhere on the board
GND: C1.2, J1.1, J1.3, J1.5, J1.7, J1.9, J1.11, J1.13, J1.15, J1.17, J1.19, J1.21, J1.23, J1.25, J1.27, J1.29, J1.31, J1.33, U2.7 (GND); also elsewhere on the board
INDEX_DRV: R21.2, U2.1 (1A); also elsewhere on the board
MOTEA_IN: R48.2; also elsewhere on the board
MOTEB_IN: R51.2; also elsewhere on the board
PIN4_IN: R59.2; also elsewhere on the board
PIN6_IN: R60.2; also elsewhere on the board
RDATA_DRV: R24.2, U2.9 (4A); also elsewhere on the board
SIDE1_IN: R56.2; also elsewhere on the board
STEP_IN: R53.2; also elsewhere on the board
TRK00_DRV: R22.2, U2.3 (2A); also elsewhere on the board
WDATA_IN: R54.2; also elsewhere on the board
WGATE_IN: R55.2; also elsewhere on the board
WPT_DRV: R23.2, U2.5 (3A); also elsewhere on the board

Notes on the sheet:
The floppy interface, as rev B. Inputs: a 10k pull-up to 3.3 V always, and a 1k to PC_TERM, which J7's jumper joins to 3.3 V for a real PC (909 R); then 1k in series to the GPIO (R47-R56), which limits the current a host driving a line high can push into the RP2350 while it's unpowered (under 5 mA)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
J1: odd pins GND; 4 and 6 read only.
J7: jumper on for a real PC or an Amiga (1k termination); off for the Greaseweazle/FeatherWing host (10k).
R21-R26 hold the SN7407's inputs high (lines released) from power-on until the firmware drives them: the RP2350's pins start as inputs with a weak pull-down.

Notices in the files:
parts and their libraries:
Abracon AOTA-B201610S3R3-101-T, 3.3 uH, 2016, polarity marked. From Raspberry Pi's RP2350 minimal design (MIT licence). Pad 1 to the 1.1 V side.
0402 capacitor with Raspberry Pi's wide pad layout (RP2350 minimal design, MIT licence).
